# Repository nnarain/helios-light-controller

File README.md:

# Helios Light Controller

ESP32 based light strip controller.

Usage
-----

TODO

Hardware
--------

This repo contains schematics and PCB layouts for the ESP light controller.

Install submodules to pull in external KiCAD libraries.

```
$ git submodule update --init --recursive
```

Checkout the [release](https://github.com/nnarain/helios-light-controller/releases) page for KiCAD outputs.

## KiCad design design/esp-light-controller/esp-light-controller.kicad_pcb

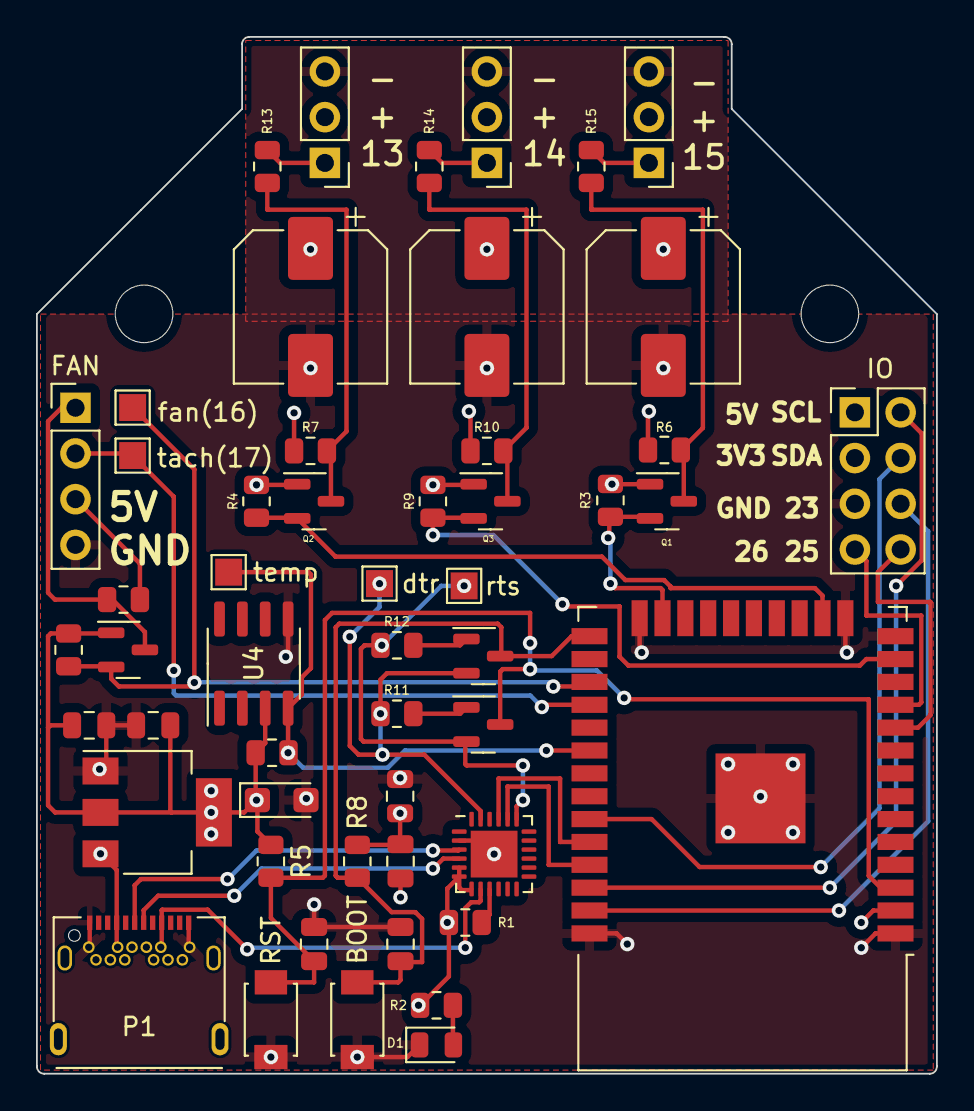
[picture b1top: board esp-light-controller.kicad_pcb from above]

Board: 4 copper layers, 50.0 x 57.6 mm, 52 parts (0 on the bottom side), 33 nets.

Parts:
C1: 1uF; C_0805_2012Metric
C2, C5, C6, C7: 100nF; C_0805_2012Metric
C3: 10uF; C_0805_2012Metric
C4: 22uF; CP_EIA-3216-18_Kemet-A
C8, C9, C10: 1000uF; CP_Elec_8x10
D1: PWR; LED_0805_2012Metric
FAN: FAN; PinHeader_1x04_P2.54mm_Vertical
J1: LED0; PinHeader_1x03_P2.54mm_Vertical
J2: LED1; PinHeader_1x03_P2.54mm_Vertical
J3: LED2; PinHeader_1x03_P2.54mm_Vertical
J5: IO; PinHeader_2x04_P2.54mm_Vertical
P1: USB_C_Plug_USB2.0; TYPE-C-31-M-04
Q1, Q2, Q3, Q4, Q5, Q6: 2N7002; SOT-23
R1, R18: 4.7k; R_0805_2012Metric
R2: 330; R_0805_2012Metric
R3, R4, R5, R6, R7, R8, R9, R10, R11, R12, R16, R17: 10k; R_0805_2012Metric
R13, R14, R15: 100; R_0805_2012Metric
SW1: RST; TS-1088-AR02016
SW2: BOOT; TS-1088-AR02016
TP1: temp; TestPoint_Pad_1.5x1.5mm
TP2: fan(16); TestPoint_Pad_1.5x1.5mm
TP3: dtr; TestPoint_Pad_1.5x1.5mm
TP4: rts; TestPoint_Pad_1.5x1.5mm
TP5: tach(17); TestPoint_Pad_1.5x1.5mm
U1: CP2104; QFN-24-1EP_4x4mm_P0.5mm_EP2.6x2.6mm
U2: AMS1117-3.3; SOT-223-3_TabPin2
U3: ESP32-WROOM-32
U4: DS18B20Z; SOIC-8_3.9x4.9mm_P1.27mm

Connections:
+3V3: C1.1, C2.1, C3.1, C4.1, C5.1, J5.3, Q1.1 (G), Q2.1 (G), Q3.1 (G), Q6.1 (G), R1.1, R2.1, R3.1, R4.1, R5.1, R8.1, R9.1, R16.1, R18.1, U1.5 (VIO), U1.6 (VDD), U1.7 (REGIN), U2.2 (VO), U3.2 (VDD), U4.3 (VDD)
+5V: C8.1, C9.1, C10.1, FAN.3, J1.2, J2.2, J3.2, J5.1, P1.A4 (VBUS), P1.A9 (VBUS), P1.B4 (VBUS), P1.B9 (VBUS), R6.1, R7.1, R10.1, R17.1, U1.8 (VBUS), U2.3 (VI)
/dtr: Q5.2 (S), R11.1, TP3.1, U1.23 (~DTR)
/en: C6.1, Q4.3 (D), R5.2, SW1.1, U3.3 (EN)
/esp_rx: U1.21 (TXD), U3.34 (RXD0/IO3)
/esp_tx: U1.20 (RXD), U3.35 (TXD0/IO1)
/fan: FAN.1, Q6.3 (D), R17.2
/fanctl: Q6.2 (S), R16.2, TP2.1, U3.27 (IO16)
/io0: C7.1, Q5.3 (D), R8.2, SW2.1, U3.25 (IO0)
/io23: J5.6, U3.37 (IO23)
/io25: J5.8, U3.10 (IO25)
/io26: J5.7, U3.11 (IO26)
/led0: Q2.3 (D), R7.2, R13.1
/led1: Q3.3 (D), R10.2, R14.1
/led2: Q1.3 (D), R6.2, R15.1
/ledctl0: Q2.2 (S), R4.2, U3.16 (IO13)
/ledctl1: Q3.2 (S), R9.2, U3.13 (IO14)
/ledctl2: Q1.2 (S), R3.2, U3.23 (IO15)
/rts: Q4.2 (S), R12.1, TP4.1, U1.19 (~RTS)
/scl: J5.2, U3.36 (IO22)
/sda: J5.4, U3.33 (IO21)
/tach: FAN.2, TP5.1, U3.28 (IO17)
/usb_dm: P1.A7 (D-), U1.4 (D-)
/usb_dp: P1.A6 (D+), U1.3 (D+)
GND: C1.2, C2.2, C3.2, C4.2, C5.2, C6.2, C7.2, C8.2, C9.2, C10.2, D1.1 (K), FAN.4, J1.3, J2.3, J3.3, J5.5, P1.A1 (GND), P1.A12 (GND), P1.B1 (GND), P1.B12 (GND), SW1.2, SW2.2, U1.2 (GND), U1.25 (GND), U2.1 (GND), U3.1 (GND), U3.14 (IO12), U3.15 (GND), U3.24 (IO2), U3.38 (GND), U3.39 (GND), U4.5 (GND)
unnamed: D1.2 (A), R2.2
unnamed: J1.1, R13.2
unnamed: J2.1, R14.2
unnamed: J3.1, R15.2
unnamed: Q4.1 (G), R11.2
unnamed: Q5.1 (G), R12.2
unnamed: R1.2, U1.9 (~RST)
unnamed: R18.2, TP1.1, U3.30 (IO18), U4.4 (DQ)

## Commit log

2019-08-02 logs
2019-08-03 Resolves #1. Use the topic prefix to create topics names
2019-08-04 Resolves #5. Publish state.
2019-08-04 Resolves #6. Added README.
2019-08-04 Resolves #7. Restore light state after power cycle.
2019-08-04 Resolves #9. Publish state topic with retain flag set to true
2019-08-04 Resolves #8. Added KiCAD files.
2019-08-05 Update pinout for USB connector
2019-08-05 Resolves #10. Removed use of absolute paths in project settings.
2019-08-08 Resolves #11. Added PCB Layout.
2019-08-10 Logging module
2019-08-11 Resolves #3. Added logging function.
2019-08-14 Resolves #14. Remove infinite retry loop for MQTT connection.
2019-09-28 build kicad-tools
2019-09-29 Not realyy a change..
2019-09-29 changed name
2019-09-29 Resolves #13. KiCAD automation
2019-09-29 Use FX library
2019-09-30 Resolves #21. Add effects from WS2812FX.
2019-09-30 Resolves #23. Save color state as JsonObject.
2019-10-01 Resolves #24. Set animation speed and brightness.
2019-10-01 Check if attribute exists before loading initial state
2019-10-01 NOP schematic update..
2019-10-07 try will external lib
2019-10-08 Resolves #29. Added third party KiCAD as a submodule.
2019-10-08 Restore CI config
2019-10-08 Update submodules
2019-10-10 Resolves #27. Improve retry logic for WiFi and MQTT
2019-10-13 Resolves #30. Update readme.
2019-10-20 Resolves #25. Remove unnecessary JSON serialization
2019-10-21 Resolves #4. Script to set basic controller options.
2020-07-28 Update to surface mount components
2020-07-30 Version 2 design
2020-08-10 ESPHome example. Remove arduino firmware.
2020-08-10 Resolves #35. Asset path.
2022-04-14 Update to kicad 6
2022-04-30 ESP32 based design
2022-05-01 update pwr led to more available part
2022-05-06 Resolves #38. Select USB-C Connector that works for JLCPCB assembly
2022-05-08 Restore silkscreen part references
2022-05-18 deploy: 479c8c66d226c6a8a3be95f889a89baf58992842
2022-09-05 Resolves #39, #40, #43. Rev D.
2022-09-05 M3 mounting holes
2022-09-05 Fix datasheet for fan header
2022-09-05 update cache
2022-09-05 deploy: 0eef7703fd9c01a0a069a60083dbc4739e438706
2022-09-25 rev e
2022-09-25 remove datasheet from io header
2022-09-25 docs
2022-09-25 deploy: d20c722c59070c9af097cc986c1ca85e0942f099
2022-09-28 Rename project
2024-09-03 Bump actions/download-artifact from 2 to 4.1.7 in /.github/workflows
    Bumps [actions/download-artifact](https://github.com/actions/download-artifact) from 2 to 4.1.7.
    - [Release notes](https://github.com/actions/download-artifact/releases)
    - [Commits](https://github.com/actions/download-artifact/compare/v2...v4.1.7)
    ---
    updated-dependencies:
    - dependency-name: actions/download-artifact
